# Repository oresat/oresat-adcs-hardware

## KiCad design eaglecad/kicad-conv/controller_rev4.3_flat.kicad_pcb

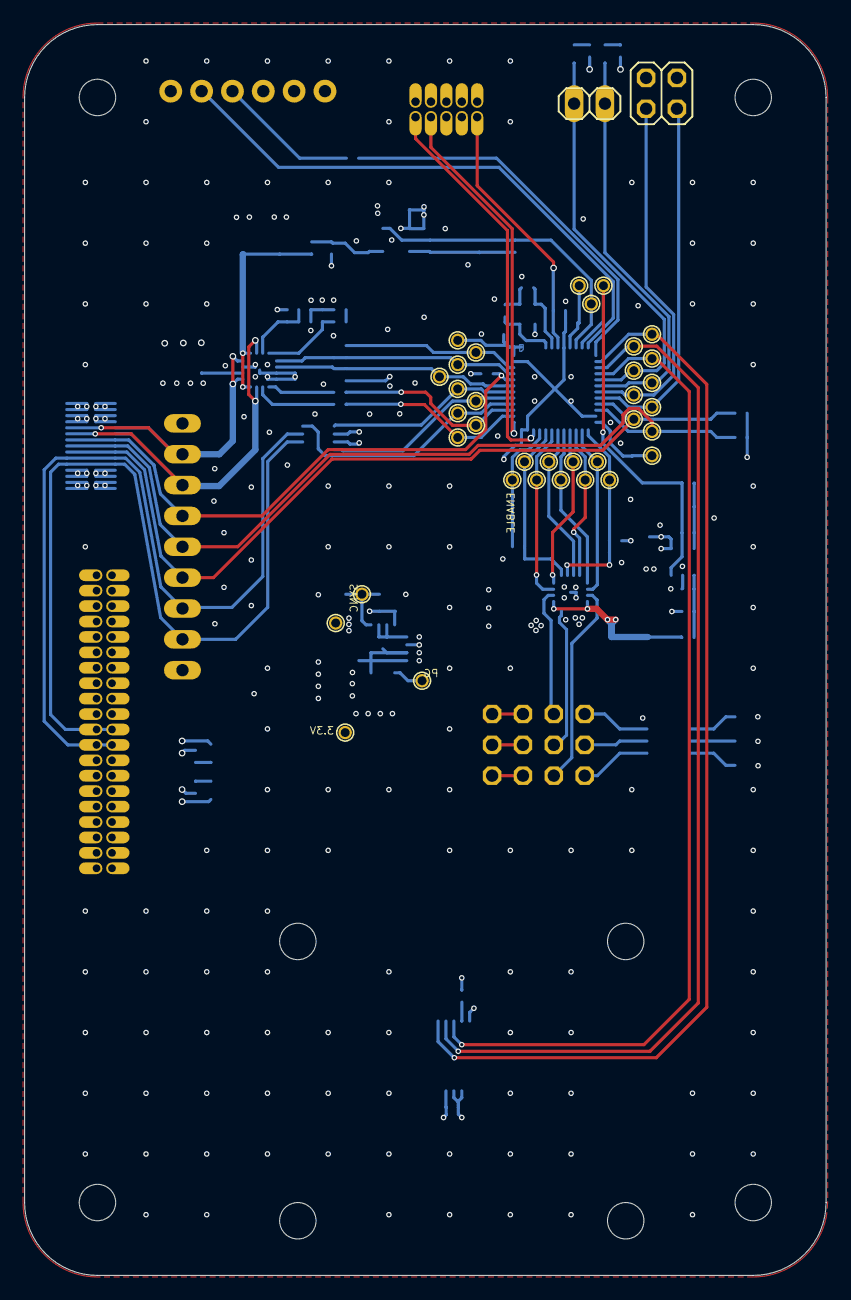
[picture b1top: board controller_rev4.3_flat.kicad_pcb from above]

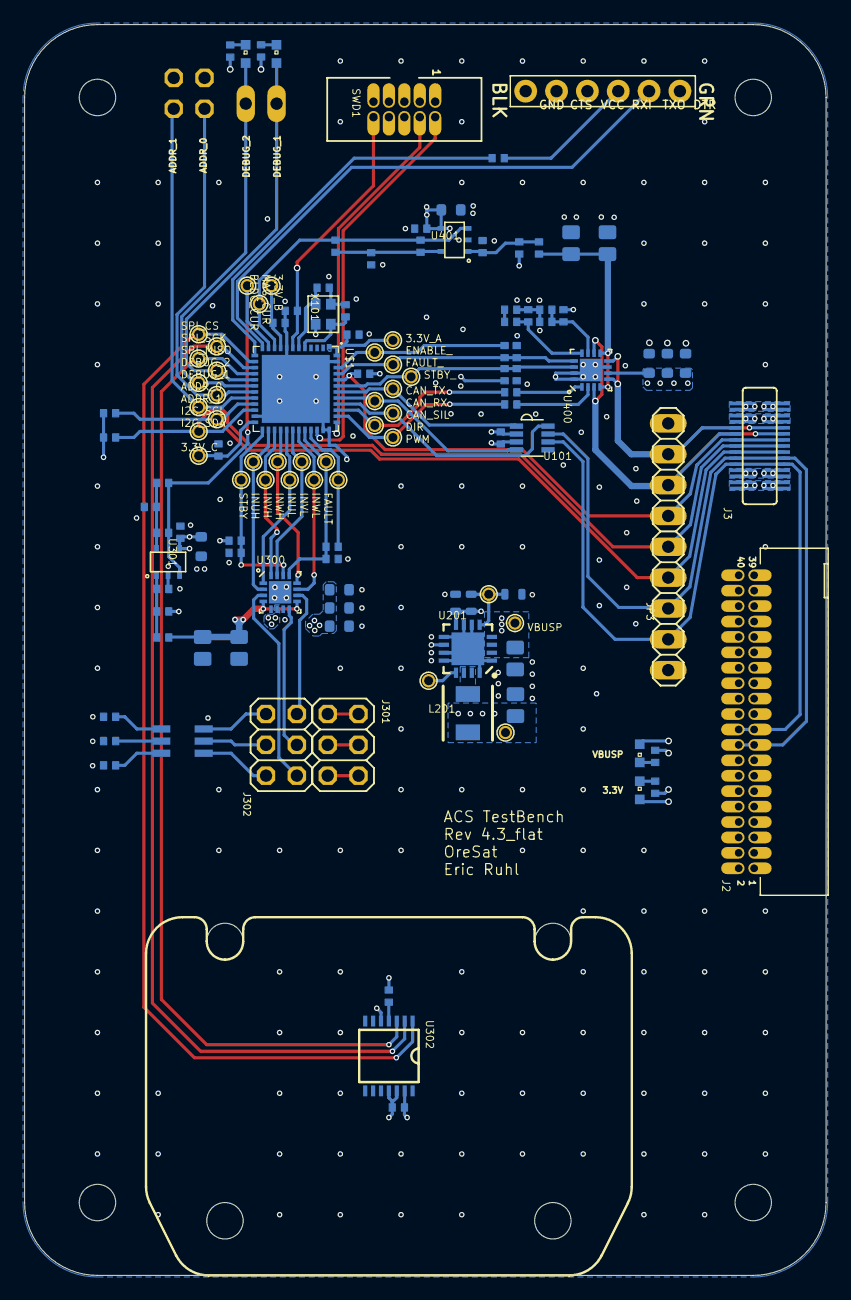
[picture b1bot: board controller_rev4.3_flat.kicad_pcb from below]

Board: 4 copper layers, 66.0 x 103.0 mm, 134 parts (93 on the bottom side), 75 nets.

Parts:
3.3V: TEST-POINT-LARGE-SQUARE; 1X01
3.3V_A, 3.3V_B, 3.3V_C: TEST-POINT-LARGE; 1X01
@HOLE0, @HOLE1, @HOLE2, @HOLE3, @HOLE4, @HOLE5, @HOLE6, @HOLE7: (no value)
ADDR_0, ADDR_1: TEST-POINT-LARGE; 1X01
BLDC_CUR: TEST-POINT-LARGE; 1X01
C101, C102, C106, C107, C307, C310, C408: 100n; .0402-B-NOSILK
C103, C305, C405: 10n; .0402-B-NOSILK
C104, C105: 20p; .0402-B-NOSILK
C201: 10u; .0805-B-NOSILK
C202: 1u; .0603-C-NOSILK
C203: 22u; .0805-B-NOSILK
C301, C302, C401, C402: 22u; .0603-B-NOSILK
C303, C403: 2.2u; .0603-B-NOSILK
C304, C404: 1n; .0402-B-NOSILK
C306, C409: 4.7u; .0603-B-NOSILK
C308, C309, C410, C411: 680p; .0402-B-NOSILK
C406: 2.2n; .0402-B-NOSILK
C407: 22n; .0402-B-NOSILK
CAN_RX: TEST-POINT-LARGE; 1X01
CAN_SIL: TEST-POINT-LARGE; 1X01
CAN_TX: TEST-POINT-LARGE; 1X01
DEBUG_1, DEBUG_2: TEST-POINT-LARGE; 1X01
DIR: TEST-POINT-LARGE; 1X01
ENABLE: TEST-POINT-LARGE; 1X01
ENABLE_: TEST-POINT-LARGE; 1X01
FAULT: TEST-POINT-LARGE; 1X01
FAULT_: TEST-POINT-LARGE; 1X01
I2C_SCL, I2C_SDA: TEST-POINT-LARGE; 1X01
INUH: TEST-POINT-LARGE; 1X01
INUL: TEST-POINT-LARGE; 1X01
INVH: TEST-POINT-LARGE; 1X01
INVL: TEST-POINT-LARGE; 1X01
INWH: TEST-POINT-LARGE; 1X01
INWL: TEST-POINT-LARGE; 1X01
J1: 6_PIN_SERIAL_TARGET_SIDE_W_SILK
J2: J-SAMTEC-TFM-120-X1-XXX-D-RA
J3: MEZZANINE_PLUG
J301, J302: 2X03
JP1: 1X02
JP2: 2X02
JP3: 1X09
L201: 6.8u; ECS-MPI4040
LED1: AMBER; CHIPLED_0603
LED2: GREEN; CHIPLED_0603
LED3, LED4: BLUE; CHIPLED_0603
LED301: CLX6E-FKC
MAG_CUR: TEST-POINT-LARGE; 1X01
PG: TEST-POINT-LARGE-SQUARE; 1X01
PWM: TEST-POINT-LARGE; 1X01
R1: 1.3k; .0402-B-NOSILK
R2, R403, R404: 330; .0402-B-NOSILK
R3, R4: 100; .0402-B-NOSILK
R7: 380; .0402-B-NOSILK
R8: 400; .0402-B-NOSILK
R9: 320; .0402-B-NOSILK
R101, R104, R309: 10k; .0402-B-NOSILK
R105, R106: 4.7k; .0402-B-NOSILK
R201: 10k; .0603-C-NOSILK
R202: NP; .0603-C-NOSILK
R301, R302, R401, R402, R406: 18k; .0402-B-NOSILK
R303, R307, R308, R409, R413, R414: 2.2k; .0402-B-NOSILK
R304, R410: 680; .0402-B-NOSILK
R305, R306, R411, R412: 0.68; .0805-B-NOSILK
R405: 100k; .0402-B-NOSILK
R407: 1k; .0402-B-NOSILK
R408: 47k; .0402-B-NOSILK
SPI_CS: TEST-POINT-LARGE; 1X01
SPI_MISO: TEST-POINT-LARGE; 1X01
SPI_SCK: TEST-POINT-LARGE; 1X01
STBY: TEST-POINT-LARGE; 1X01
STBY_: TEST-POINT-LARGE; 1X01
SWD1: 1.27MM-SWD-CONNECTOR; 1.27MM_2X5
SYNC: TEST-POINT-LARGE-SQUARE; 1X01
U101: TCAN330; SOT23-8_TI-DCN
U201: TPS62111RSA; S-PVQFN-16
U300: STSPIN230; VFQPN
U301, U401: TSV991ILT; SOT23-5
U302: AS5047P; TSSOP14
U400: STSPIN250; VFQPN
U$1: STM32L452CEU3; QFPN-48
VBUSP: TEST-POINT-LARGE-SQUARE; 1X01
X101: ABM10-16MHz; CRYSTAL_2.5X2

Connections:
3.3V: 3.3V.1, 3.3V_A.1, 3.3V_B.1, 3.3V_C.1, C101.1, C102.1, C103.1, C107.1, C203.1, C306.1, C307.1, C310.1, C408.1, C409.1, L201.2, LED2.A, R105.2, R106.2, R301.1, R303.2, R309.1, R401.1, R405.1, R409.2, SWD1.VTREF, U101.3, U201.10, U301.4, U302.11, U302.12, U401.4, U$1.1, U$1.9, U$1.24, U$1.48
250_REF: C406.1, R405.2, R406.1, U400.11
250_TOFF: R407.1, R408.1, U400.12
ADDR_0: ADDR_0.1, JP2.1, U$1.19
ADDR_1: ADDR_1.1, JP2.3, U$1.20
AS5047_MOSI: R309.2, U302.4
BLDC_CURR_FDB: BLDC_CUR.1, C309.1, R307.2, U301.3, U$1.11
BLDC_EN: ENABLE.1, R302.2, U$1.33
BLDC_FAULT: C305.1, FAULT.1, R302.1, U300.13, U$1.32
BLDC_INUH: INUH.1, U300.2, U$1.26
BLDC_INUL: INUL.1, U300.1, U$1.29
BLDC_INVH: INVH.1, U300.16, U$1.27
BLDC_INVL: INVL.1, U300.15, U$1.30
BLDC_INWH: INWH.1, U300.12, U$1.28
BLDC_INWL: INWL.1, U300.11, U$1.31
BLDC_STBY: C304.1, R301.2, STBY.1, U300.14, U$1.25
BOOT: J3.P$9, J3.P$22, JP3.6, R101.2, U$1.44
B_IN+: C308.1, R303.1, R304.2, U301.1
B_IN-: C309.2, R307.1, R308.2, U301.5
CAN_H: J2.17, J2.18, J3.P$6, J3.P$25, JP3.3, U101.7
CAN_L: J2.19, J2.20, J3.P$5, J3.P$26, JP3.2, U101.6
CAN_RX: CAN_RX.1, U101.4, U$1.41
CAN_SILENT: CAN_SIL.1, U101.8, U$1.40
CAN_TX: CAN_TX.1, U101.1, U$1.42
CLK1: C104.1, U$1.5, X101.3
CLK2: C105.1, U$1.6, X101.1
DEBUG_1: DEBUG_1.1, JP1.1, LED4.A, U$1.18
DEBUG_2: DEBUG_2.1, JP1.2, LED3.A, U$1.17
GND: C101.2, C102.2, C103.2, C104.2, C105.2, C106.2, C107.2, C201.2, C202.2, C203.2, C301.2, C302.2, C303.2, C304.2, C305.2, C306.2, C307.2, C308.2, C310.2, C401.2, C402.2, C403.2, C404.2, C405.2, C406.2, C407.2, C408.2, C409.2, C410.2, J1.P$6, J2.27, J2.28, J2.29, J2.30, J2.31, J2.32, J2.37, J2.38, J3.P$1, J3.P$2, J3.P$14, J3.P$15, J3.P$16, J3.P$17, J3.P$29, J3.P$30, JP2.2, JP2.4, JP3.9, R1.1, R2.1, R3.1, R4.1, R7.1, R8.1, R9.1, R101.1, R202.1, R305.1, R306.1, R308.1, R406.2, R408.2, R411.2, R412.2, R414.1, SWD1.GND, SWD1.GND@2, U101.2, U201.1, U201.6, U201.7, U201.9, U201.11, U201.12, U201.16, U201.PAD, U300.7, U300.EPAD, U301.2, U302.5, U302.13, U400.7, U400.15, U400.16, U400.EPAD, U401.2, U$1.8, U$1.23, U$1.35, U$1.36, U$1.47, U$1.EPAD, X101.2, X101.4
I2C_SCL: I2C_SCL.1, J3.P$7, J3.P$24, JP3.4, R105.1, U$1.21
I2C_SDA: I2C_SDA.1, J3.P$8, J3.P$23, JP3.5, R106.1, U$1.22
MAG_CURR_FDB: C411.1, MAG_CUR.1, R413.2, U401.3, U$1.10
MAG_DIR: DIR.1, R403.2, U$1.39
MAG_EN: ENABLE_.1, R402.2, U$1.46
MAG_FAULT: C405.1, FAULT_.1, R402.1, U400.13, U$1.45
MAG_PWM: PWM.1, R404.2, U$1.38
MAG_STBY: C404.1, R401.2, STBY_.1, U400.14, U$1.43
M_IN+: C410.1, R409.1, R410.2, U401.1
M_IN-: C411.2, R413.1, R414.2, U401.5
M_PH: R403.1, U400.1
M_PWM: R404.1, U400.2
unnamed: J302.2, LED301.P$4
unnamed: J302.4, LED301.P$5
unnamed: J302.6, LED301.P$6
unnamed: J301.5, J301.6
unnamed: LED4.C, R4.2
unnamed: LED3.C, R3.2
unnamed: LED1.C, R1.2
unnamed: LED2.C, R2.2
unnamed: J301.3, J301.4
unnamed: J301.1, J301.2
unnamed: LED301.P$1, R7.2
unnamed: LED301.P$2, R8.2
unnamed: LED301.P$3, R9.2
NRST: C106.1, SWD1.!RESET, U$1.7
OUT1: J3.P$10, J3.P$21, JP3.7, U400.3, U400.10
OUT2: J3.P$11, J3.P$20, JP3.8, U400.5, U400.8
SENSE_BLDC: R304.1, R305.2, R306.2, U300.4, U300.9
SENSE_MAG: R410.1, R411.1, R412.1, U400.4, U400.9
SPI1_CS: SPI_CS.1, U302.1, U$1.14
SPI1_MISO: SPI_MISO.1, U302.3, U$1.16
SPI1_SCK: SPI_SCK.1, U302.2, U$1.15
SWCLK: SWD1.SWDCLK, U$1.37
SWDIO: SWD1.SWDIO, U$1.34
TOFF1: C407.1, R407.2
TPS62111-PG2: PG.1, U201.13
TPS62111-SYNC2: R201.1, R202.2, SYNC.1, U201.5
TPS62111_SW1: L201.1, U201.14, U201.15
U: J302.1, U300.3
UART_RX: R104.2, U$1.13
UART_RX1: J1.P$3, R104.1
UART_TX: J1.P$2, U$1.12
V: J302.3, U300.8
VBUSP: C201.1, C202.1, C301.1, C302.1, C303.1, C401.1, C402.1, C403.1, J1.P$4, J2.21, J2.22, J2.23, J2.24, J2.25, J2.26, J3.P$3, J3.P$4, J3.P$12, J3.P$13, J3.P$18, J3.P$19, J3.P$27, J3.P$28, JP3.1, LED1.A, R201.2, U201.2, U201.3, U201.4, U201.8, U300.6, U400.6, VBUSP.1
W: J302.5, U300.10

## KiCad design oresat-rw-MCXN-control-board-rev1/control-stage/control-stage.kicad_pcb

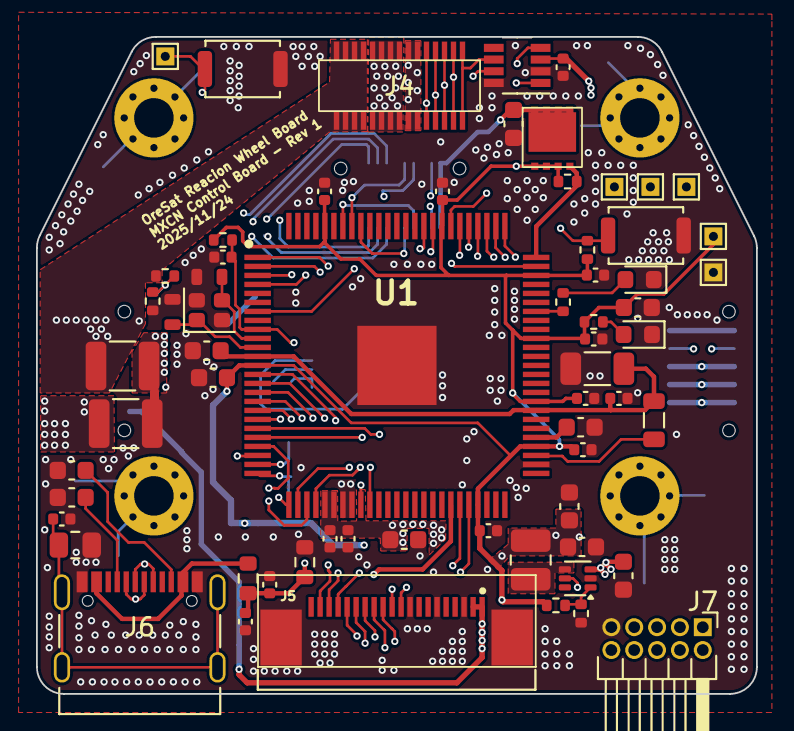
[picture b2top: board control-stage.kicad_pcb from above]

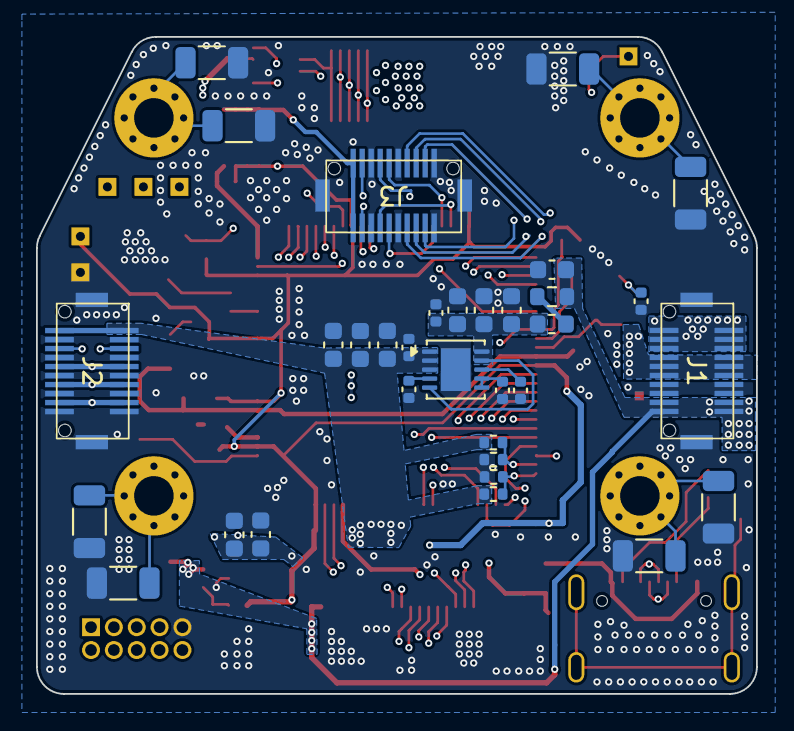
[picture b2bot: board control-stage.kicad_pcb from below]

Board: 6 copper layers, 40.0 x 36.5 mm, 99 parts (33 on the bottom side), 69 nets.

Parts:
C1, C15, C25, C26, C28, C29, C33: 10u; C_0603_1608Metric
C2, C8, C10: 4.7u; C_0603_1608Metric
C3, C4, C6, C7, C9, C11, C13, C14, C16, C17, C18, C21, C23, C24, C30, C35: 100n; C_0402_1005Metric
C5, C31, C32, C34: 1u; C_0402_1005Metric
C12: 6.8u; C_1206_3216Metric
C19, C20: 47u; C_1210_3225Metric
C22: 10p; C_0402_1005Metric
C27, C36, C37, C38, C39, C40, C41, C42: 22u; C_0603_1608Metric
C43, C44: 4.7p; 0603-C-NOSILK
D1, D2: Green; LED_0603_1608Metric
FB1: MPZ1608B471ATA00; L_0603_1608Metric
H1: Board_Def; top-board-def-rev7.1
J1: Power Mezz; 10132798-021100LF
J2: Analog Mezz; 10132798-021100LF
J3: Phase Mezz; 10132798-021100LF
J4: ADCS Mezz; 0555600307
J5: Debug; J-TE_2-1734592-0
J6: USB-C; USB_C_Receptacle_Palconn_UTC16-G
J7: PROBE; PinHeader_2x05_P1.27mm_Horizontal
L1: 1.5u; L_0805_2012Metric
L2: 2.2u; L_1008_2520Metric
NT1: NetTie; NetTie_ADCS
Q1: TPN4R712MD,L1Q; TSON-Advance
R1: 17.8k/1%; R_0603_1608Metric
R2: 33k/1%; R_0603_1608Metric
R3, R5: 10k/NTC; R_0402_1005Metric
R4, R6, R7, R21: 10k; R_0402_1005Metric
R8, R9, R10, R11, R12, R13, R14, R15: THJP1206ABT1; R_1206_3216Metric
R16: 5.1k/0.1%; R_0402_1005Metric
R17: 3.3k/0.1%; R_0402_1005Metric
R18: 1M; R_0805_2012Metric
R19, R20: 5.11k; C_0603_1608Metric
R22: 2.2; R_0603_1608Metric
R23, R25: 100k/1%; R_0402_1005Metric
R24: 442k/1%; R_0402_1005Metric
R26, R27: 100; R_0402_1005Metric
SW1: BOOT0; SW_Push_SPST_NO_Alps_SKRK
SW2: RESET; SW_Push_SPST_NO_Alps_SKRK
TP1, TP2, TP3, TP4, TP5, TP6: TestPoint_Alt; TestPoint_THTPad_1.0x1.0mm_Drill0.5mm
U1: MCXN947VKLT; MCXN947KVLT-QFP50P1600X1600X160-101N
U2: TCAN330; SOT-23-8-Fixed
U3: ADP7156ACPZ; DFN-10-1EP_3x3mm_P0.5mm_EP1.65x2.38mm
U4: TLV62569DRL; SOT-563
Y1: 24 MHz; Crystal_SMD_2016-4Pin_2.0x1.6mm

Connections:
5V_FILT: C26.1, C28.1, C29.1, C30.1, FB1.2, U3.5 (EN), U3.9 (VIN), U3.10 (VIN)
+3V3: C1.2, C2.2, C4.2, C6.2, C7.2, C9.2, C11.2, C14.2, C16.2, C21.1, C37.2, C39.2, C41.2, C42.2, J5.11 (VTARGET), L2.2, Q1.1 (S), R7.1, R21.2, R23.2, R24.2, R27.1, TP1.1, U1.13 (VDD_LDO_CORE/VDD/VDD_P2), U1.34 (VDD_P4), U1.47 (VDD_BAT), U1.54 (VDD_DCDC/VDD_LDO_SYS), U1.59 (VDD_P3), U1.66 (VDD_P3), U1.73 (VDD_P3), U1.83 (VDD), U1.96 (VDD), U2.3 (VCC)
+3V3A: C10.1, C13.1, C17.1, C35.2, C36.2, C38.2, C40.2, J2.1, J2.20, R3.1, R5.1, U1.30 (VDD_ANA), U1.31 (VREFH), U3.1 (VOUT), U3.2 (VOUT), U3.3 (VOUT_SENSE)
+3V3_SW: C27.2, J3.10, J3.11, Q1.3 (D)
+5V: C20.1, C25.1, C33.1, J1.9, J1.10, J1.11, J1.12, J4.17, J4.18, J4.19, J4.20, J5.1 (VBUSP), J5.2 (VBUSP), R22.1, U4.3 (VIN), U4.5 (EN)
/Power Architecture/FB: R24.1, R25.2, U4.1 (FB)
BOOT0: J4.25, J4.26, J5.17 (DEBUG-0), R7.2, SW1.2, U1.82 (ISPMODE_N)
BYP: C31.1, U3.4 (BYP)
CAN_N: J4.29, J4.30, U2.6 (CANL)
CAN_P: J4.27, J4.28, U2.7 (CANH)
CAN_RX: U1.4 (CAN0_RXD), U2.4 (RXD)
CAN_TX: U1.3 (CAN0_TXD), U2.1 (TXD)
Chassis: H1.1, R8.1, R9.1, R10.1, R11.1, R12.1, R13.1, R14.1, R15.1
DEBUG0: J7.1, U1.79 (P0_3)
DEBUG1: J7.3, U1.80 (P0_4)
DEBUG2: J7.5, U1.81 (P0_5)
DEBUG3: J7.7, U1.74 (P3_1)
DEBUG_RX: J5.12 (CARD-RX), J7.4, U1.84 (P0_16)
DEBUG_SWCLK: J5.15 (SWCLK), TP3.1, U1.77 (TCLK/SWCLK)
DEBUG_SWDIO: J5.14 (SWDIO), TP4.1, U1.76 (TMS/SWDIO)
DEBUG_SWO: J5.16 (SWO), TP5.1, U1.78 (TDO/SWO)
DEBUG_TX: J5.13 (CARD-TX), J7.2, U1.85 (P0_17)
ENC_A: J3.9, U1.20 (TRIG_IN4)
ENC_B: J3.12, U1.21 (TRIG_IN5)
GND: C1.1, C2.1, C3.1, C4.1, C5.2, C6.1, C7.1, C8.2, C9.1, C10.2, C11.1, C12.2, C13.2, C14.1, C15.2, C16.1, C17.2, C18.2, C20.2, C21.2, C22.2, C23.2, C24.2, C25.2, C26.2, C27.1, C28.2, C29.2, C30.2, C31.2, C32.2, C33.2, C34.2, C35.1, C36.1, C37.1, C38.1, C39.1, C40.1, C41.1, C42.1, C43.2, C44.2, D1.1 (K), D2.1 (K), J1.7, J1.8, J1.13, J1.14, J1.MP (MountPin), J2.2, J2.4, J2.6, J2.8, J2.10, J2.11, J2.13, J2.15, J2.17, J2.19, J2.MP (MountPin), J3.1, J3.5, J3.8, J3.13, J3.16, J3.20, J3.MP (MountPin), J5.3 (GND), J5.6 (GND), J5.9 (GND), J5.PAD1 (PAD), J5.PAD2 (PAD), J6.A1 (GND), J6.A12 (GND), J6.B1 (GND), J6.B12 (GND), J7.9, NT1.2, R2.1, R4.2, R6.2, R8.2, R9.2, R10.2, R11.2, R12.2, R13.2, R14.2, R15.2, R17.1, R18.1, R19.1, R20.1, R25.1, SW1.1, SW2.2, TP6.1, U1.32 (VREFL), U1.33 (VSS_P4), U1.52 (VSS_DCDC), U1.101 (EP), U2.2 (GND), U2.8 (S), U3.11 (GND), U4.2 (GND), Y1.2, Y1.4
unnamed: C12.1, C15.1, C18.1, L1.1, U1.12 (VDD_CORE), U1.58 (VDD_CORE)
unnamed: D1.2 (A), R27.2
unnamed: D2.2 (A), R26.2
unnamed: FB1.1, R22.2
unnamed: J6.A5 (CC1), R20.2
unnamed: J6.B5 (CC2), R19.2
unnamed: C23.1, J6.S1 (SHIELD), R18.2
unnamed: L1.2, U1.53 (DCDC_LX)
unnamed: C8.1, U1.55 (VDD_SYS)
unnamed: C3.2, C5.1, R1.1, R2.2, U1.44 (VDD_USB)
unnamed: C44.1, U1.10 (XTAL48M), Y1.3
unnamed: C43.1, U1.11 (EXTAL48M), Y1.1
unnamed: R26.1, U1.69 (P3_9)
unnamed: L2.1, U4.4 (SW)
PGND: C19.2, J1.4, J1.5, J1.6, J1.15, J1.16, J1.17, J4.9, J4.10, J4.11, J4.12, J4.13, J4.14, J4.15, J4.16, NT1.1
PHA_H: J3.2, U1.14 (P2_0)
PHA_ISNS: J2.5, J2.16, U1.22 (ADC0_A0)
PHA_L: J3.19, U1.15 (P2_1)
PHB_H: J3.3, U1.16 (P2_2)
PHB_ISNS: J2.7, J2.14, U1.26 (ADC1_A0)
PHB_L: J3.18, U1.17 (P2_3)
PHC_H: J3.4, U1.18 (P2_4)
PHC_ISNS: J2.9, J2.12, U1.28 (DAC2_OUT/ADC0_A3/ADC1_A3)
PHC_L: J3.17, U1.19 (P2_5)
REF: C34.1, U3.6 (REF_SENSE), U3.7 (REF)
RESET: C24.1, J5.10 (NRST), R21.1, SW2.1, TP2.1, U1.9 (RESET_B)
SCOPE0: J7.10, U1.27 (ADC1_B0)
SCOPE1: J7.8, U1.29 (VREFI/VREFO/ADC0_A7/ADC1_A7)
SCOPE2: J7.6, U1.35 (OPAMP0_INP0/ADC0_A5/ADC1_A5)
SPI_MISO: J3.7, U1.94 (SPI_SDI)
SPI_MOSI: J3.6, U1.92 (SPI_SDO)
SPI_SCK: J3.15, U1.93 (SPI_SCK)
SPI_nCS: J3.14, U1.7 (P1_14)
SW_3V3: Q1.2 (G), R23.1, U1.75 (P3_0)
THERM_A: J2.18, R5.2, R6.1, U1.25 (DAC1_OUT/ADC0_B4/ADC1_B4/CMP0_IN5N/CMP1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)
THERM_B: J2.3, R3.2, R4.1, U1.24 (DAC0_OUT/ADC0_A4/ADC1_A4/CMP0_IN4N/CMP1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)
UART_RX: J4.23, J4.24, J5.19 (DEBUG-2), U1.1 (ISP-UART_RXD)
UART_TX: J4.21, J4.22, J5.18 (DEBUG-1), U1.2 (ISP-UART_TXD)
USB0_DM: J6.A6 (D+), J6.B6 (D+), U1.45 (USB0_DM)
USB0_DP: J6.A7 (D-), J6.B7 (D-), U1.46 (USB0_DP)
VBUS: C19.1, J1.1, J1.2, J1.3, J1.18, J1.19, J1.20, J4.1, J4.2, J4.3, J4.4, J4.5, J4.6, J4.7, J4.8, R16.1
VBUS_VSNS: C22.1, R16.2, R17.2, U1.23 (ADC0_B0)
VREG: C32.1, U3.8 (VREG)
V_USB: J6.A4 (VBUS), J6.A9 (VBUS), J6.B4 (VBUS), J6.B9 (VBUS), R1.2

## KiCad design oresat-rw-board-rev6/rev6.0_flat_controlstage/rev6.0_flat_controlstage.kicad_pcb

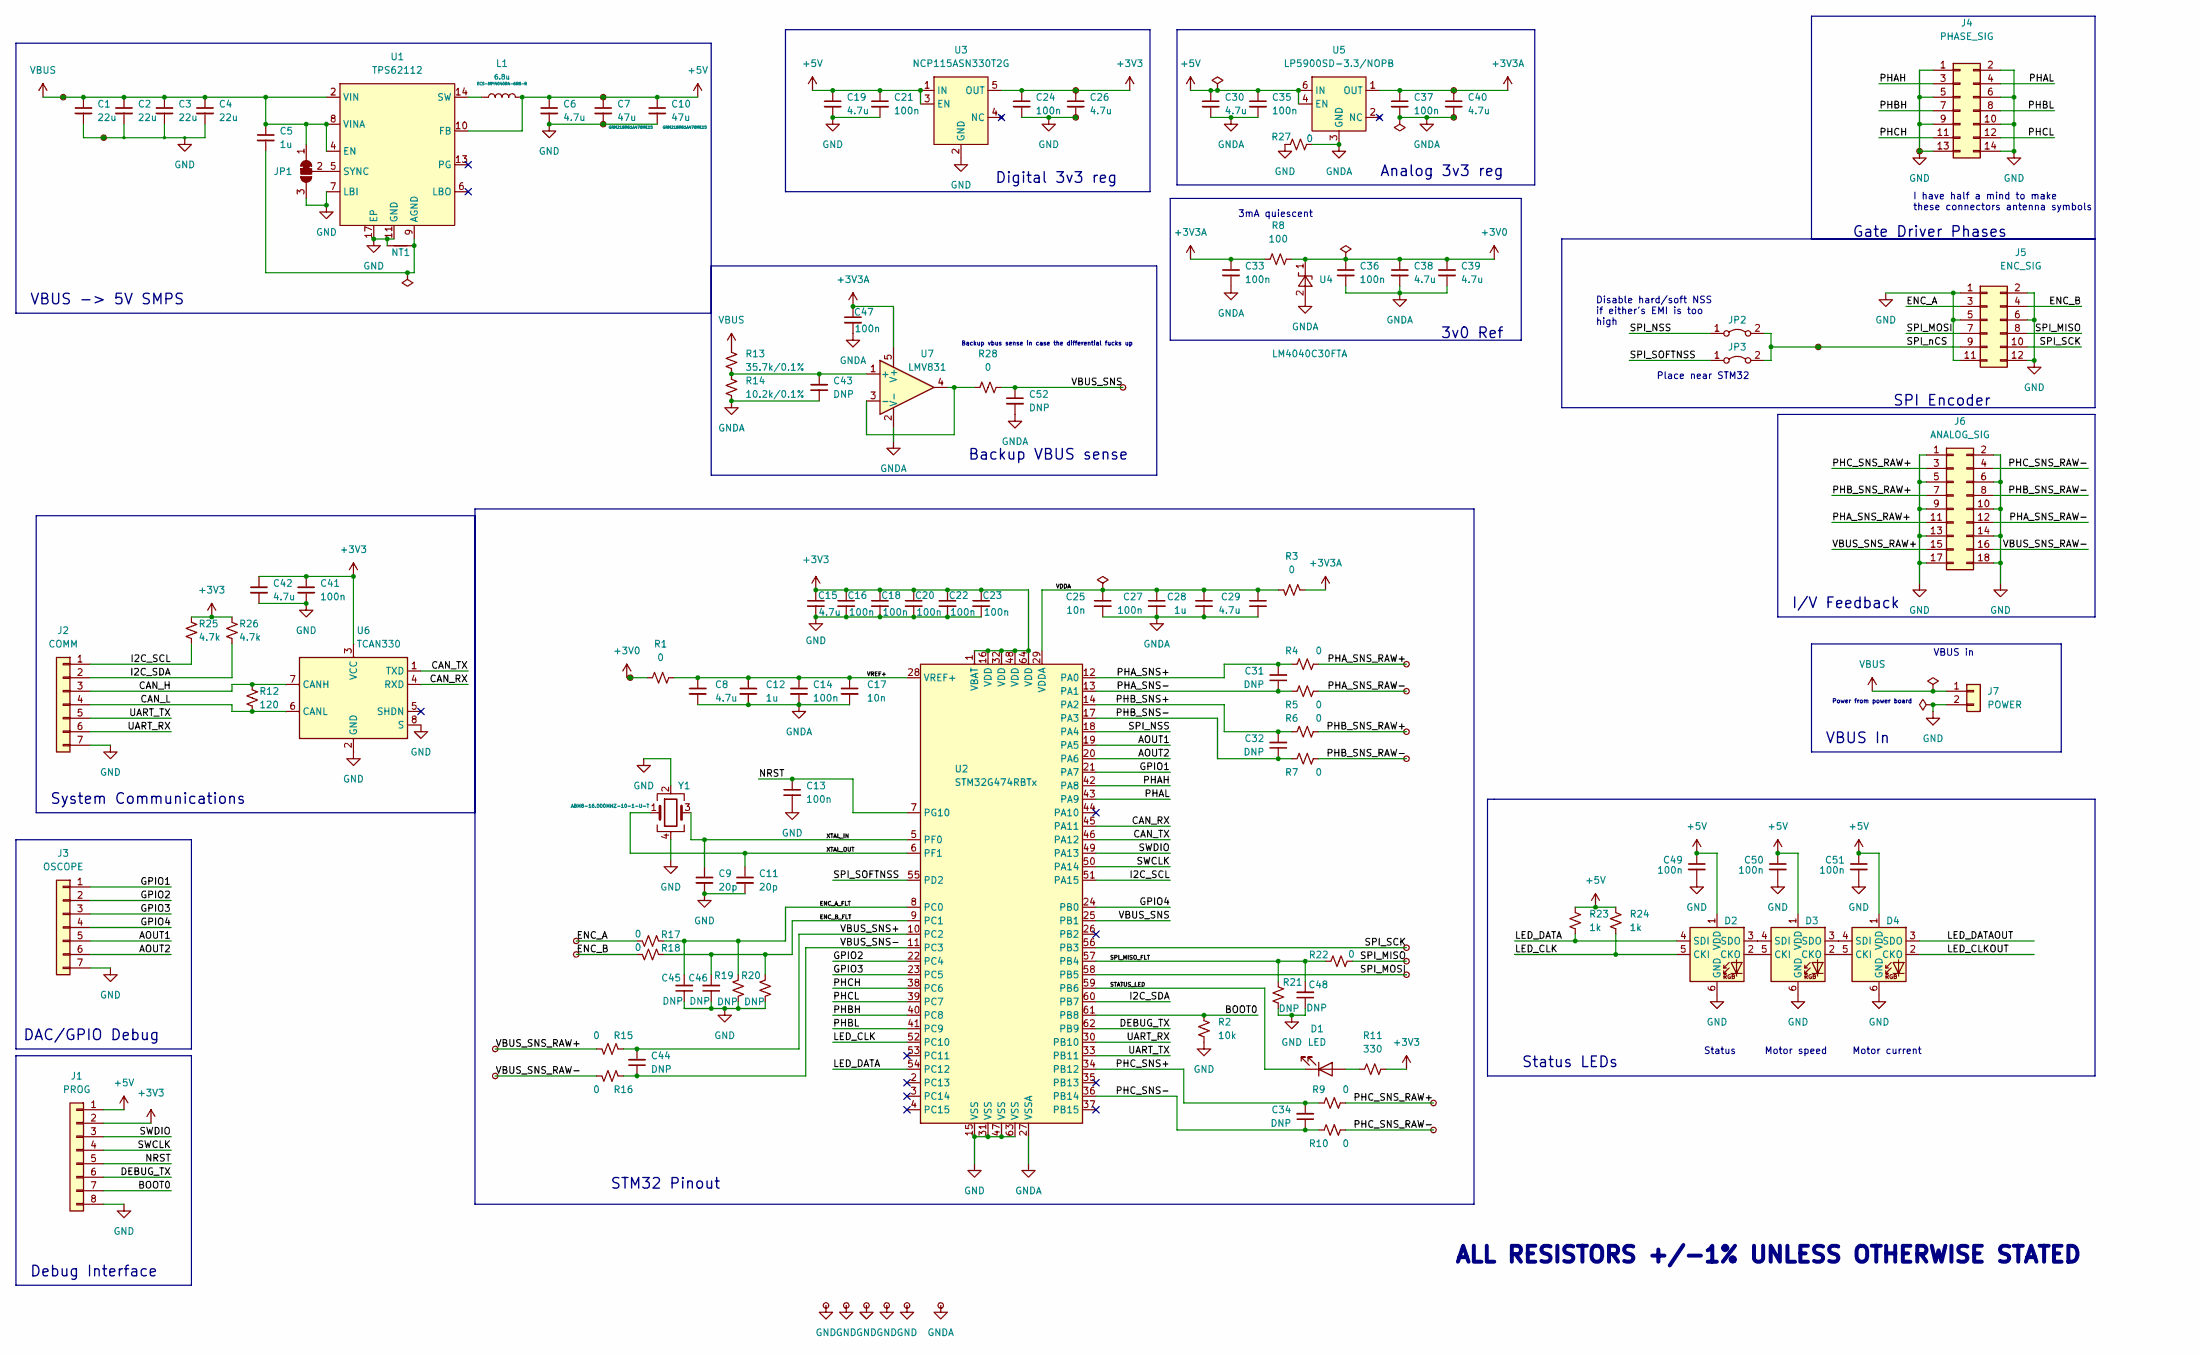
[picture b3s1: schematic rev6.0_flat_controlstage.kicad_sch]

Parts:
C1, C2, C3, C4: 22u; C_0805_2012Metric
C5: 1u; C_0603_1608Metric
C6, C8, C15, C19, C26, C29, C30, C38, C39, C40, C42: 4.7u; C_0603_1608Metric
C7, C10: 47u; C_0805_2012Metric
C9, C11: 20p; C_0603_1608Metric
C12, C28: 1u; C_0402_1005Metric
C13, C14, C16, C18, C20, C22, C23, C27: 100n; C_0402_1005Metric
C17, C25: 10n; C_0402_1005Metric
C21, C24, C33, C35, C36, C37, C41, C47, C49, C50, C51: 100n; C_0603_1608Metric
C31, C32, C34, C44, C45, C46, C48: DNP; C_0402_1005Metric
C43, C52: DNP; C_0603_1608Metric
D1: LED; LED_0603_1608Metric
D2, D3, D4: APA102-2020; APA102_2020
J1: PROG; PinHeader_1x08_P2.54mm_Vertical
J2: COMM; PinHeader_1x07_P2.54mm_Vertical
J3: OSCOPE; PinHeader_1x07_P2.54mm_Vertical
J4: PHASE_SIG; PinHeader_2x07_P2.54mm_Horizontal
J5: ENC_SIG; PinHeader_2x06_P2.54mm_Horizontal
J6: ANALOG_SIG; PinHeader_2x09_P2.54mm_Horizontal
J7: POWER; PinHeader_1x02_P2.54mm_Horizontal
JP1: SolderJumper_3_Bridged12; SolderJumper-3_P1.3mm_Bridged12_Pad1.0x1.5mm
JP2, JP3: Jumper_2_Bridged; R_0603_1608Metric
L1: 6.8u; ECS-MPI4040R4
NT1: NetTie_2; NetTie-2_SMD_Pad0.5mm
R1, R3, R27, R28: 0; R_0603_1608Metric
R2: 10k; R_0603_1608Metric
R4, R5, R6, R7, R9, R10, R15, R16, R17, R18, R22: 0; R_0402_1005Metric
R8: 100; R_0603_1608Metric
R11: 330; R_0603_1608Metric
R12: 120; R_0603_1608Metric
R13: 35.7k/0.1%; R_0603_1608Metric
R14: 10.2k/0.1%; R_0603_1608Metric
R19, R20, R21: DNP; R_0402_1005Metric
R23, R24: 1k; R_0603_1608Metric
R25, R26: 4.7k; R_0603_1608Metric
TP1, TP2, TP3, TP4, TP5, TP6, TP7, TP8, TP9, TP10, TP11, TP12, TP13, TP14, TP15, TP16, TP17, TP18, TP19, TP20, TP21, TP22, TP23, TP24, TP25, TP26, TP27, TP28, TP29, TP30, TP31: TestPoint_Small; TestPoint_Keystone_5015_Micro-Minature_3DMODEL
U1: TPS62112; QFN-16-1EP_4x4mm_P0.65mm_EP2.7x2.7mm
U2: STM32G474RBTx; LQFP-64_10x10mm_P0.5mm
U3: NCP115ASN330T2G; TSOT-23-5
U4: LM4040C30FTA; SOT-23
U5: LP5900SD-3.3/NOPB; TI-WSON-6-2.2x2.5
U6: TCAN330; SOT-23-8-Fixed
U7: LMV831; SOT-353_SC-70-5
Y1: Crystal_GND24; Crystal_SMD_3225-4Pin_3.2x2.5mm

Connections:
+3V0: C36.1, C38.1, C39.1, R1.1, R8.2, TP9.1, U4.1 (K)
+3V3: C15.1, C16.1, C18.1, C20.1, C22.1, C23.1, C24.1, C26.1, C41.1, C42.1, J1.2, R11.2, R25.1, R26.1, TP11.1, U2.1 (VBAT), U2.16 (VDD), U2.32 (VDD), U2.48 (VDD), U2.64 (VDD), U3.5 (OUT), U6.3 (VCC)
+3V3A: C33.1, C37.1, C40.1, C47.1, R3.1, R8.1, TP24.1, U5.1 (OUT), U7.5 (V+)
+5V: C6.1, C7.1, C10.1, C19.1, C21.1, C30.1, C35.1, C49.1, C50.1, C51.1, D2.1 (VDD), D3.1 (VDD), D4.1 (VDD), J1.1, L1.2, R23.1, R24.1, TP7.1, U1.10 (FB), U3.1 (IN), U3.3 (EN), U5.4 (EN), U5.6 (IN)
/AOUT1: J3.5, U2.19 (PA5)
/AOUT2: J3.6, U2.20 (PA6)
/BOOT0: J1.7, R2.1, U2.61 (PB8)
/CAN_H: J2.3, R12.1, U6.7 (CANH)
/CAN_L: J2.4, R12.2, U6.6 (CANL)
/CAN_RX: U2.45 (PA11), U6.4 (RXD)
/CAN_TX: U2.46 (PA12), U6.1 (TXD)
/DEBUG_TX: J1.6, U2.62 (PB9)
/ENC_A: J5.3, R17.2, TP5.1
/ENC_A_FLT: C45.2, R17.1, R19.1, U2.8 (PC0)
/ENC_B: J5.4, R18.2, TP6.1
/ENC_B_FLT: C46.2, R18.1, R20.1, U2.9 (PC1)
/GPIO1: J3.1, U2.21 (PA7)
/GPIO2: J3.2, U2.22 (PC4)
/GPIO3: J3.3, U2.23 (PC5)
/GPIO4: J3.4, U2.24 (PB0)
/I2C_SCL: J2.1, R25.2, U2.51 (PA15)
/I2C_SDA: J2.2, R26.2, U2.60 (PB7)
/LED_CLK: D2.5 (CKI), R24.2, U2.52 (PC10)
/LED_CLKOUT: D4.2 (CKO)
/LED_DATA: D2.4 (SDI), R23.2, U2.54 (PC12)
/LED_DATAOUT: D4.3 (SDO)
/NRST: C13.1, J1.5, U2.7 (PG10)
/PHAH: J4.3, U2.42 (PA8)
/PHAL: J4.4, U2.43 (PA9)
/PHA_SNS+: C31.2, R4.1, U2.12 (PA0)
/PHA_SNS-: C31.1, R5.1, U2.13 (PA1)
/PHA_SNS_RAW+: J6.11, R4.2, TP15.1
/PHA_SNS_RAW-: J6.12, R5.2, TP16.1
/PHBH: J4.7, U2.40 (PC8)
/PHBL: J4.8, U2.41 (PC9)
/PHB_SNS+: C32.2, R6.1, U2.14 (PA2)
/PHB_SNS-: C32.1, R7.1, U2.17 (PA3)
/PHB_SNS_RAW+: J6.7, R6.2, TP17.1
/PHB_SNS_RAW-: J6.8, R7.2, TP18.1
/PHCH: J4.11, U2.38 (PC6)
/PHCL: J4.12, U2.39 (PC7)
/PHC_SNS+: C34.2, R9.1, U2.34 (PB12)
/PHC_SNS-: C34.1, R10.1, U2.36 (PB14)
/PHC_SNS_RAW+: J6.3, R9.2, TP22.1
/PHC_SNS_RAW-: J6.4, R10.2, TP23.1
/SPI_MISO: J5.8, R22.2, TP20.1
/SPI_MISO_FLT: C48.2, R21.1, R22.1, U2.57 (PB4)
/SPI_MOSI: J5.7, TP21.1, U2.58 (PB5)
/SPI_NSS: JP2.1 (A), U2.18 (PA4)
/SPI_SCK: J5.10, TP19.1, U2.56 (PB3)
/SPI_SOFTNSS: JP3.1 (A), U2.55 (PD2)
/SPI_nCS: J5.9, JP2.2 (B), JP3.2 (B), TP26.1
/STATUS_LED: D1.1 (K), U2.59 (PB6)
/SWCLK: J1.4, U2.50 (PA14)
/SWDIO: J1.3, U2.49 (PA13)
/UART_RX: J2.6, U2.30 (PB10)
/UART_TX: J2.5, U2.33 (PB11)
/VBUS_SNS: C52.1, R28.2, TP13.1, U2.25 (PB1)
/VBUS_SNS+: C44.2, R15.1, U2.10 (PC2)
/VBUS_SNS-: C44.1, R16.1, U2.11 (PC3)
/VBUS_SNS_RAW+: J6.15, R15.2, TP3.1
/VBUS_SNS_RAW-: J6.16, R16.2, TP4.1
/VDDA: C25.1, C27.1, C28.1, C29.1, R3.2, U2.29 (VDDA)
/VREF+: C8.1, C12.1, C14.1, C17.1, R1.2, U2.28 (VREF+)
/XTAL_IN: C9.1, U2.5 (PF0), Y1.3
/XTAL_OUT: C11.1, U2.6 (PF1), Y1.1
GND: C1.2, C2.2, C3.2, C4.2, C6.2, C7.2, C9.2, C10.2, C11.2, C13.2, C15.2, C16.2, C18.2, C19.2, C20.2, C21.2, C22.2, C23.2, C24.2, C26.2, C41.2, C42.2, C45.1, C46.1, C48.1, C49.2, C50.2, C51.2, D2.6 (GND), D3.6 (GND), D4.6 (GND), J1.8, J2.7, J3.7, J4.1, J4.2, J4.5, J4.6, J4.9, J4.10, J4.13, J4.14, J5.1, J5.2, J5.5, J5.6, J5.11, J5.12, J6.1, J6.2, J6.5, J6.6, J6.9, J6.10, J6.13, J6.14, J6.17, J6.18, J7.2, JP1.3 (B), NT1.1, R2.2, R19.2, R20.2, R21.2, R27.1, TP2.1, TP8.1, TP10.1, TP12.1, TP14.1, TP27.1, TP28.1, TP29.1, TP30.1, U1.1 (PGND), U1.7 (LBI), U1.11 (GND), U1.12 (GND), U1.16 (PGND), U1.17 (EP), U2.15 (VSS), U2.31 (VSS), U2.47 (VSS), U2.63 (VSS), U3.2 (GND), U6.2 (GND), U6.8 (S), Y1.2, Y1.4
GNDA: C8.2, C12.2, C14.2, C17.2, C25.2, C27.2, C28.2, C29.2, C30.2, C33.2, C35.2, C36.2, C37.2, C38.2, C39.2, C40.2, C43.2, C47.2, C52.2, R14.2, R27.2, TP25.1, TP31.1, U2.27 (VSSA), U4.2 (A), U5.3 (GND), U5.7 (GND), U7.2 (V-)
unnamed: C5.2, NT1.2, U1.9 (AGND)
unnamed: C43.1, R13.2, R14.1, U7.1 (+)
unnamed: D1.2 (A), R11.1
unnamed: D2.2 (CKO), D3.5 (CKI)
unnamed: D2.3 (SDO), D3.4 (SDI)
unnamed: D3.2 (CKO), D4.5 (CKI)
unnamed: D3.3 (SDO), D4.4 (SDI)
unnamed: JP1.2 (C), U1.5 (SYNC)
unnamed: L1.1, U1.14 (SW), U1.15 (SW)
unnamed: R28.1, U7.3 (-), U7.4
VBUS: C1.1, C2.1, C3.1, C4.1, C5.1, J7.1, JP1.1 (A), R13.1, TP1.1, U1.2 (VIN), U1.3 (VIN), U1.4 (EN), U1.8 (VINA)

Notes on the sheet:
Debug Interface
System Communications
3v0 Ref
VBUS -> 5V SMPS
DAC/GPIO Debug
Motor speed
VBUS In
Gate Driver Phases
Status
3mA quiescent
Status LEDs
Motor current
Place near STM32
Analog 3v3 reg
Power from power board
Disable hard/soft NSS if either's EMI is too high
ALL RESISTORS +/-1% UNLESS OTHERWISE STATED
VBUS in
Backup VBUS sense
Backup vbus sense in case the differential fucks up
I/V Feedback
STM32 Pinout
I have half a mind to make these connectors antenna symbols
SPI Encoder
Digital 3v3 reg

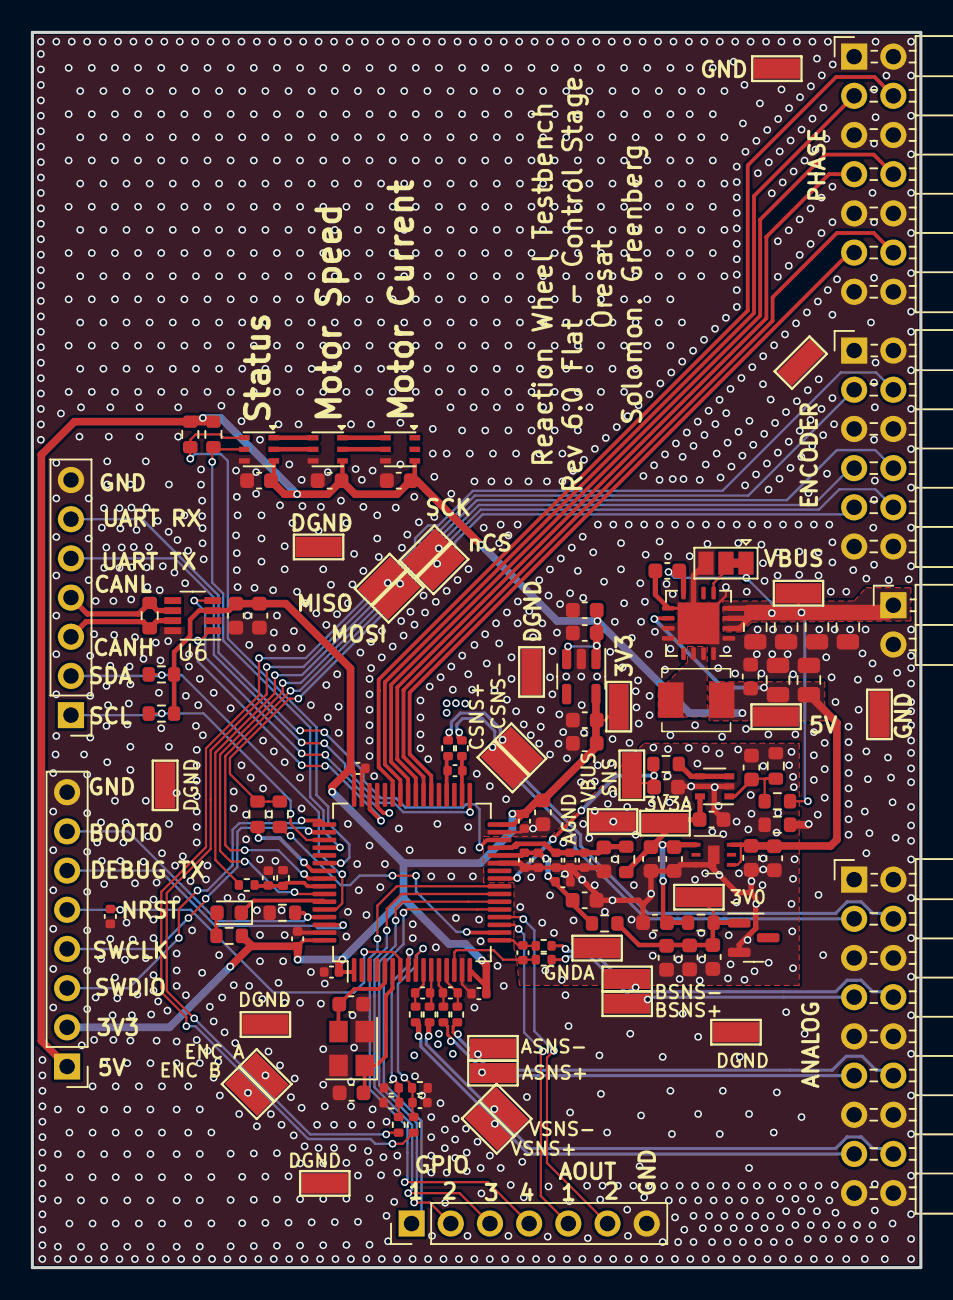
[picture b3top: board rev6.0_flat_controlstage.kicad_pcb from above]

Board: 4 copper layers, 57.6 x 80.1 mm, 135 parts (0 on the bottom side), 77 nets.
